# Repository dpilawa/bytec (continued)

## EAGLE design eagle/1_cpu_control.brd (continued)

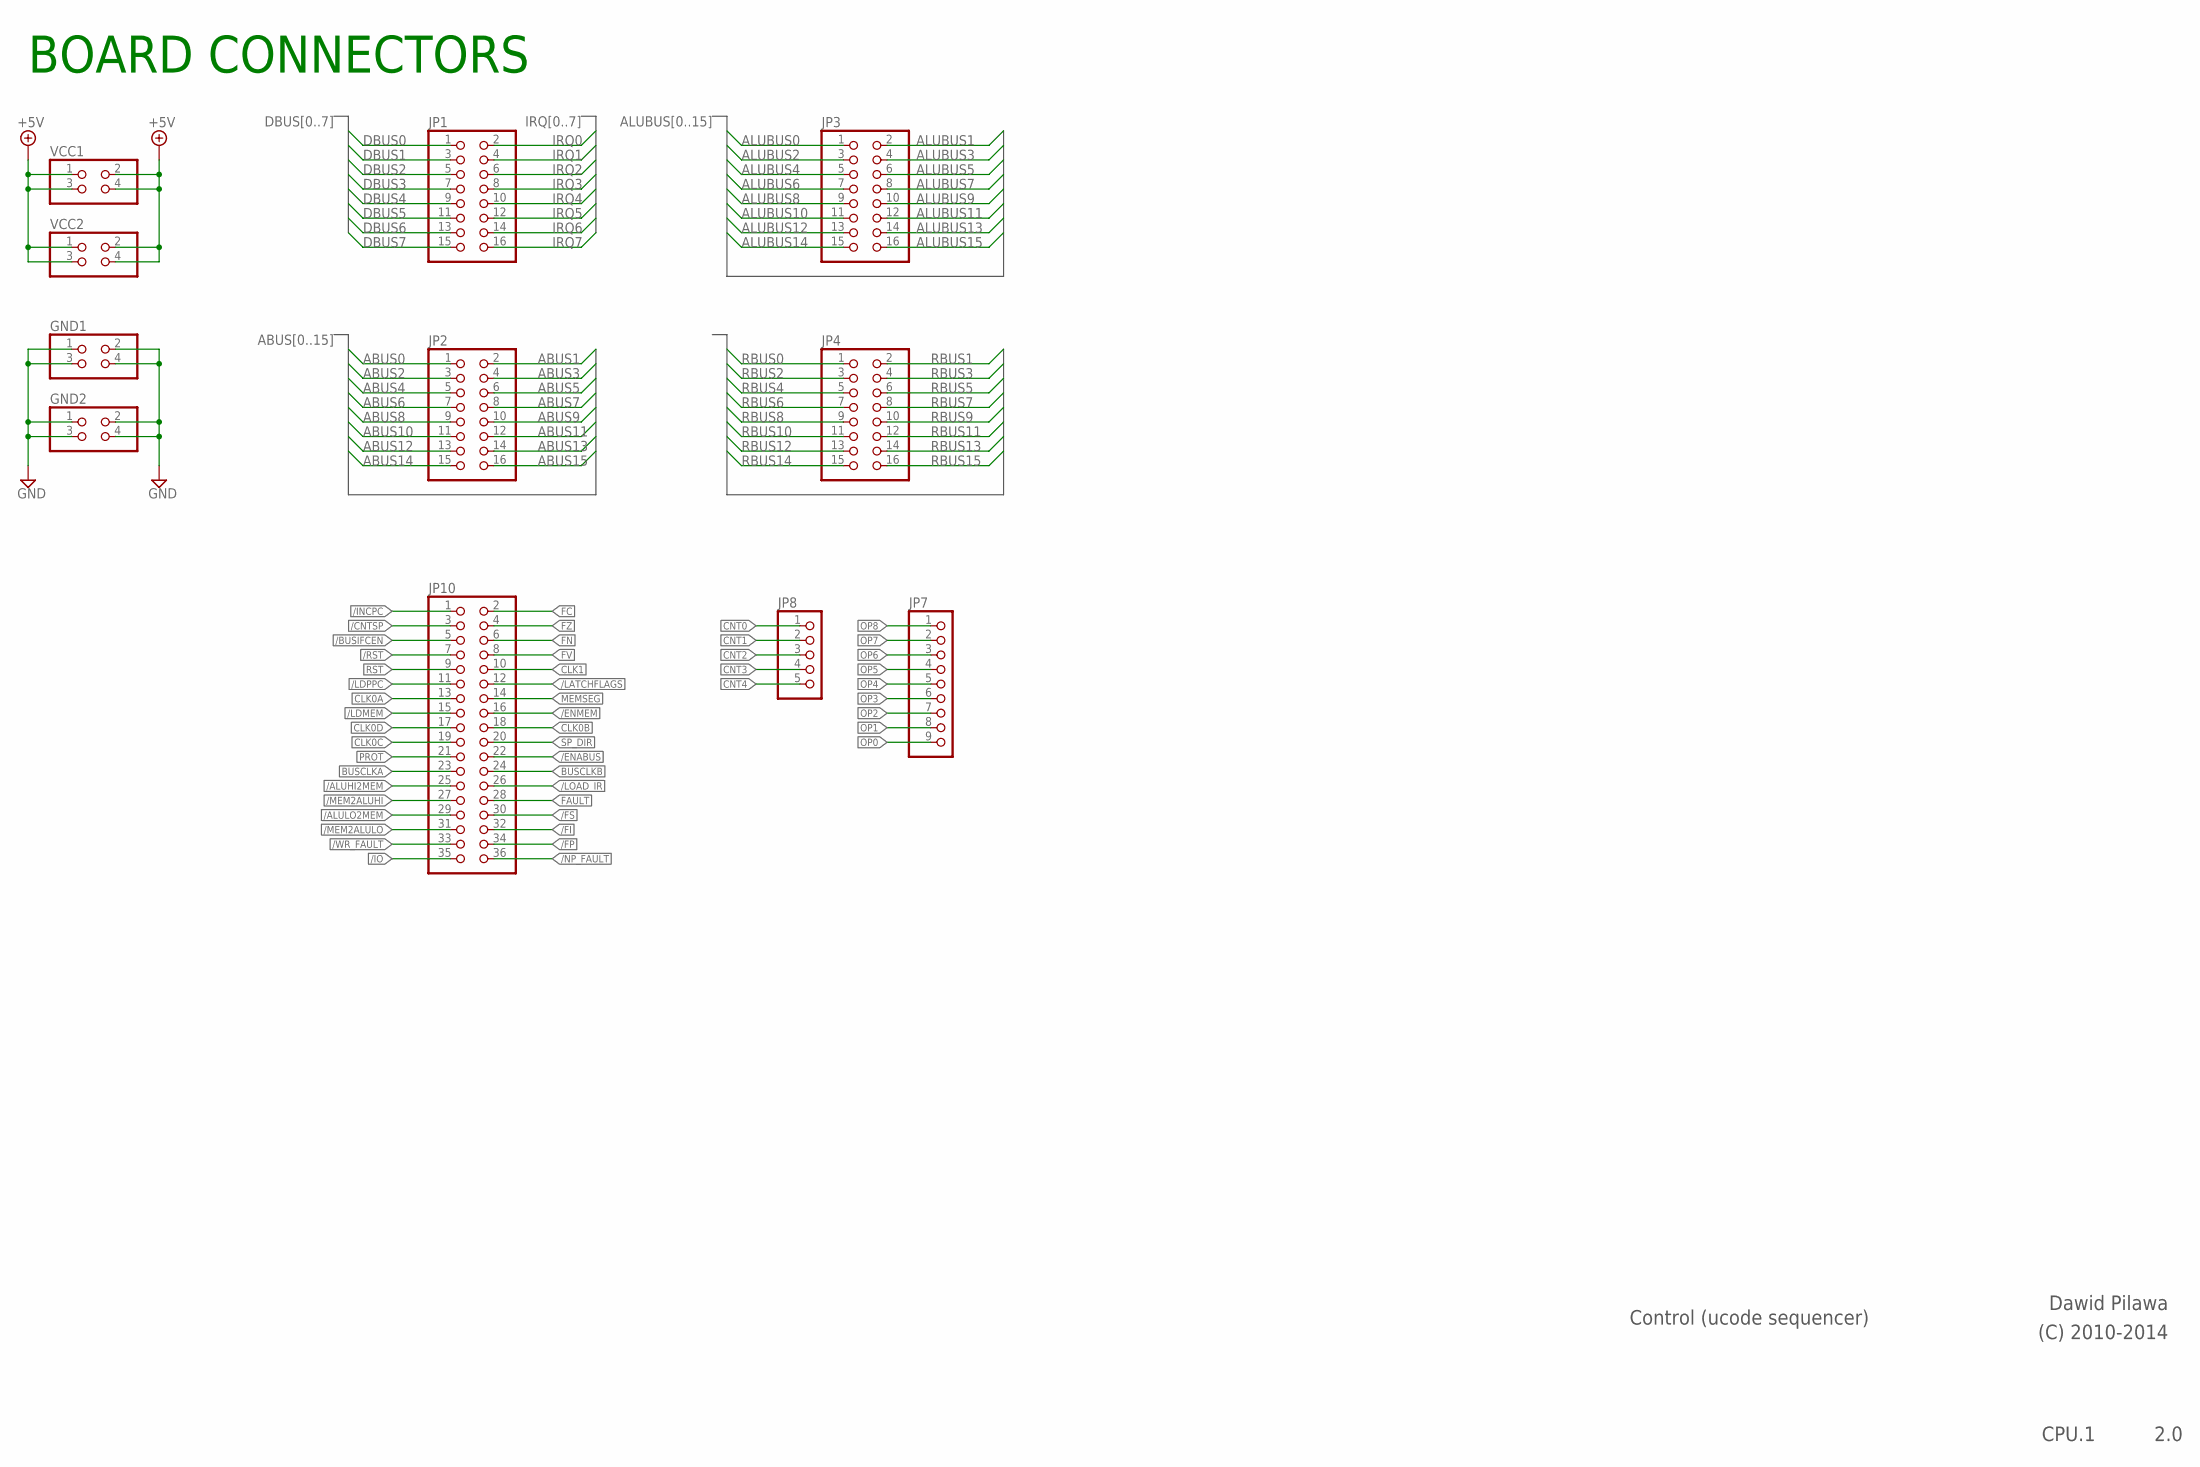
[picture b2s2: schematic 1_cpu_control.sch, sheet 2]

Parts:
GND1, GND2: PINHD-2X2; 2X02
JP1, JP2, JP3, JP4: PINHD-2X8; 2X08
JP7: PINHD-1X9; 1X09
JP8: PINHD-1X5; 1X05
JP10: PINHD-2X18; 2X18
VCC1, VCC2: PINHD-2X2; 2X02

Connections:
+5V: VCC1.1, VCC1.2, VCC1.3, VCC1.4, VCC2.1, VCC2.2, VCC2.3, VCC2.4; also elsewhere on the board
/ALUHI2MEM: JP10.25
/ALULO2MEM: JP10.29
/BUSIFCEN: JP10.5; also elsewhere on the board
/CNTSP: JP10.3
/ENABUS: JP10.22
/ENMEM: JP10.16
/FI: JP10.32; also elsewhere on the board
/FP: JP10.34
/FS: JP10.30; also elsewhere on the board
/INCPC: JP10.1
/IO: JP10.35
/LATCHFLAGS: JP10.12; also elsewhere on the board
/LDMEM: JP10.15
/LDPPC: JP10.11; also elsewhere on the board
/LOAD_IR: JP10.26; also elsewhere on the board
/MEM2ALUHI: JP10.27
/MEM2ALULO: JP10.31
/NP_FAULT: JP10.36; also elsewhere on the board
/RST: JP10.7; also elsewhere on the board
/WR_FAULT: JP10.33; also elsewhere on the board
ABUS0: JP2.1
ABUS1: JP2.2
ABUS2: JP2.3
ABUS3: JP2.4
ABUS4: JP2.5
ABUS5: JP2.6
ABUS6: JP2.7
ABUS7: JP2.8
ABUS8: JP2.9
ABUS9: JP2.10
ABUS10: JP2.11
ABUS11: JP2.12
ABUS12: JP2.13
ABUS13: JP2.14
ABUS14: JP2.15
ABUS15: JP2.16
ALUBUS0: JP3.1
ALUBUS1: JP3.2
ALUBUS2: JP3.3
ALUBUS3: JP3.4
ALUBUS4: JP3.5
ALUBUS5: JP3.6
ALUBUS6: JP3.7
ALUBUS7: JP3.8
ALUBUS8: JP3.9
ALUBUS9: JP3.10
ALUBUS10: JP3.11
ALUBUS11: JP3.12
ALUBUS12: JP3.13
ALUBUS13: JP3.14
ALUBUS14: JP3.15
ALUBUS15: JP3.16
BUSCLKA: JP10.23; also elsewhere on the board
BUSCLKB: JP10.24
CLK0A: JP10.13; also elsewhere on the board
CLK0B: JP10.18
CLK0C: JP10.19
CLK0D: JP10.17
CLK1: JP10.10
CNT0: JP8.1; also elsewhere on the board
CNT1: JP8.2; also elsewhere on the board
CNT2: JP8.3; also elsewhere on the board
CNT3: JP8.4; also elsewhere on the board
CNT4: JP8.5; also elsewhere on the board
DBUS0: JP1.1; also elsewhere on the board
DBUS1: JP1.3; also elsewhere on the board
DBUS2: JP1.5; also elsewhere on the board
DBUS3: JP1.7; also elsewhere on the board
DBUS4: JP1.9; also elsewhere on the board
DBUS5: JP1.11; also elsewhere on the board
DBUS6: JP1.13; also elsewhere on the board
DBUS7: JP1.15; also elsewhere on the board
FAULT: JP10.28; also elsewhere on the board
FC: JP10.2
FN: JP10.6
FV: JP10.8
FZ: JP10.4
GND: GND1.1, GND1.2, GND1.3, GND1.4, GND2.1, GND2.2, GND2.3, GND2.4; also elsewhere on the board
IRQ0: JP1.2; also elsewhere on the board
IRQ1: JP1.4; also elsewhere on the board
IRQ2: JP1.6; also elsewhere on the board
IRQ3: JP1.8; also elsewhere on the board
IRQ4: JP1.10; also elsewhere on the board
IRQ5: JP1.12; also elsewhere on the board
IRQ6: JP1.14; also elsewhere on the board
IRQ7: JP1.16; also elsewhere on the board
MEMSEG: JP10.14
OP0: JP7.9; also elsewhere on the board
OP1: JP7.8; also elsewhere on the board
OP2: JP7.7; also elsewhere on the board
OP3: JP7.6; also elsewhere on the board
OP4: JP7.5; also elsewhere on the board
OP5: JP7.4; also elsewhere on the board
OP6: JP7.3; also elsewhere on the board
OP7: JP7.2; also elsewhere on the board
OP8: JP7.1; also elsewhere on the board
PROT: JP10.21; also elsewhere on the board
RBUS0: JP4.1
RBUS1: JP4.2
RBUS2: JP4.3
RBUS3: JP4.4
RBUS4: JP4.5
RBUS5: JP4.6
RBUS6: JP4.7
RBUS7: JP4.8
RBUS8: JP4.9
RBUS9: JP4.10
RBUS10: JP4.11
RBUS11: JP4.12
RBUS12: JP4.13
RBUS13: JP4.14
RBUS14: JP4.15
RBUS15: JP4.16
RST: JP10.9; also elsewhere on the board
SP_DIR: JP10.20

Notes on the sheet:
Control (ucode sequencer)
2.0
Dawid Pilawa
(C) 2010-2014
CPU.1
BOARD CONNECTORS

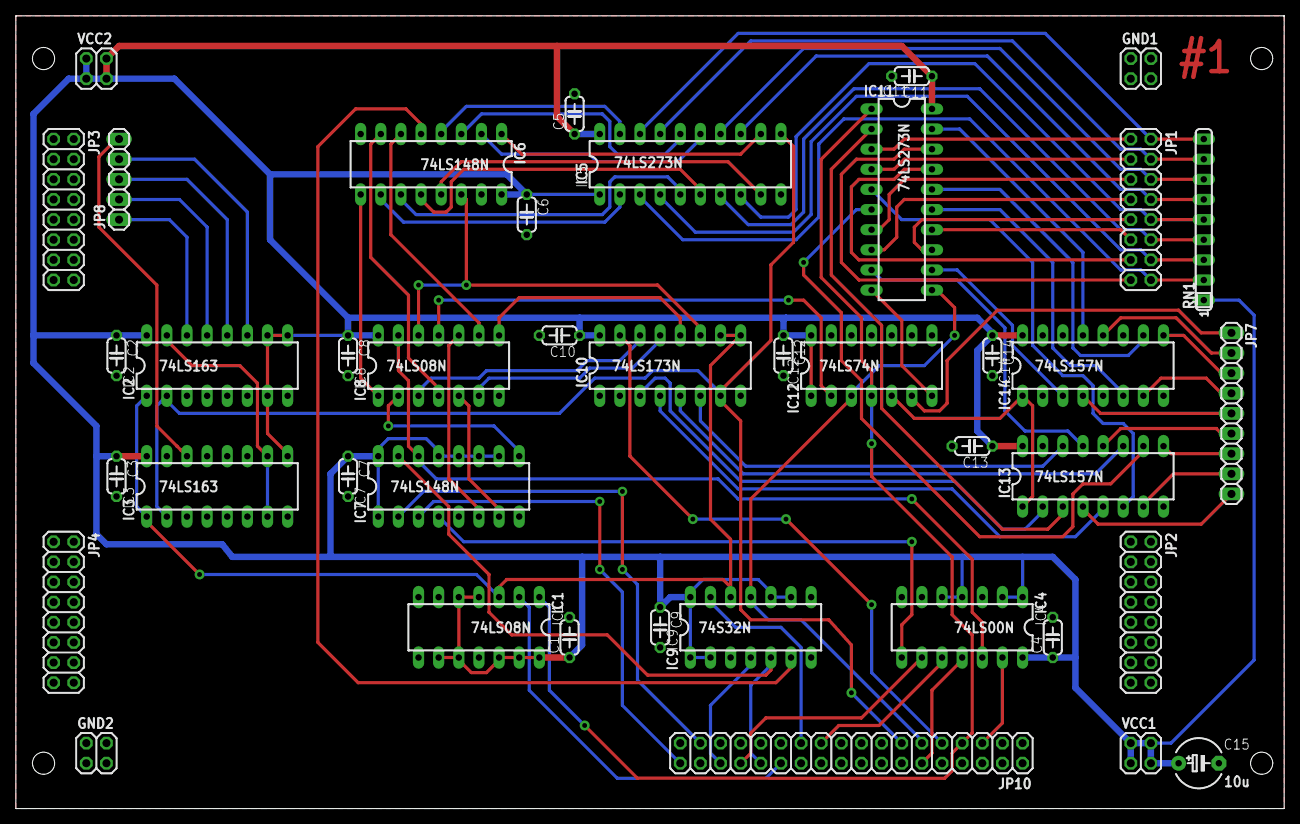
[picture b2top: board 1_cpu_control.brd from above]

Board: 2 copper layers, 160.0 x 100.0 mm, 41 parts (0 on the bottom side), 83 nets.

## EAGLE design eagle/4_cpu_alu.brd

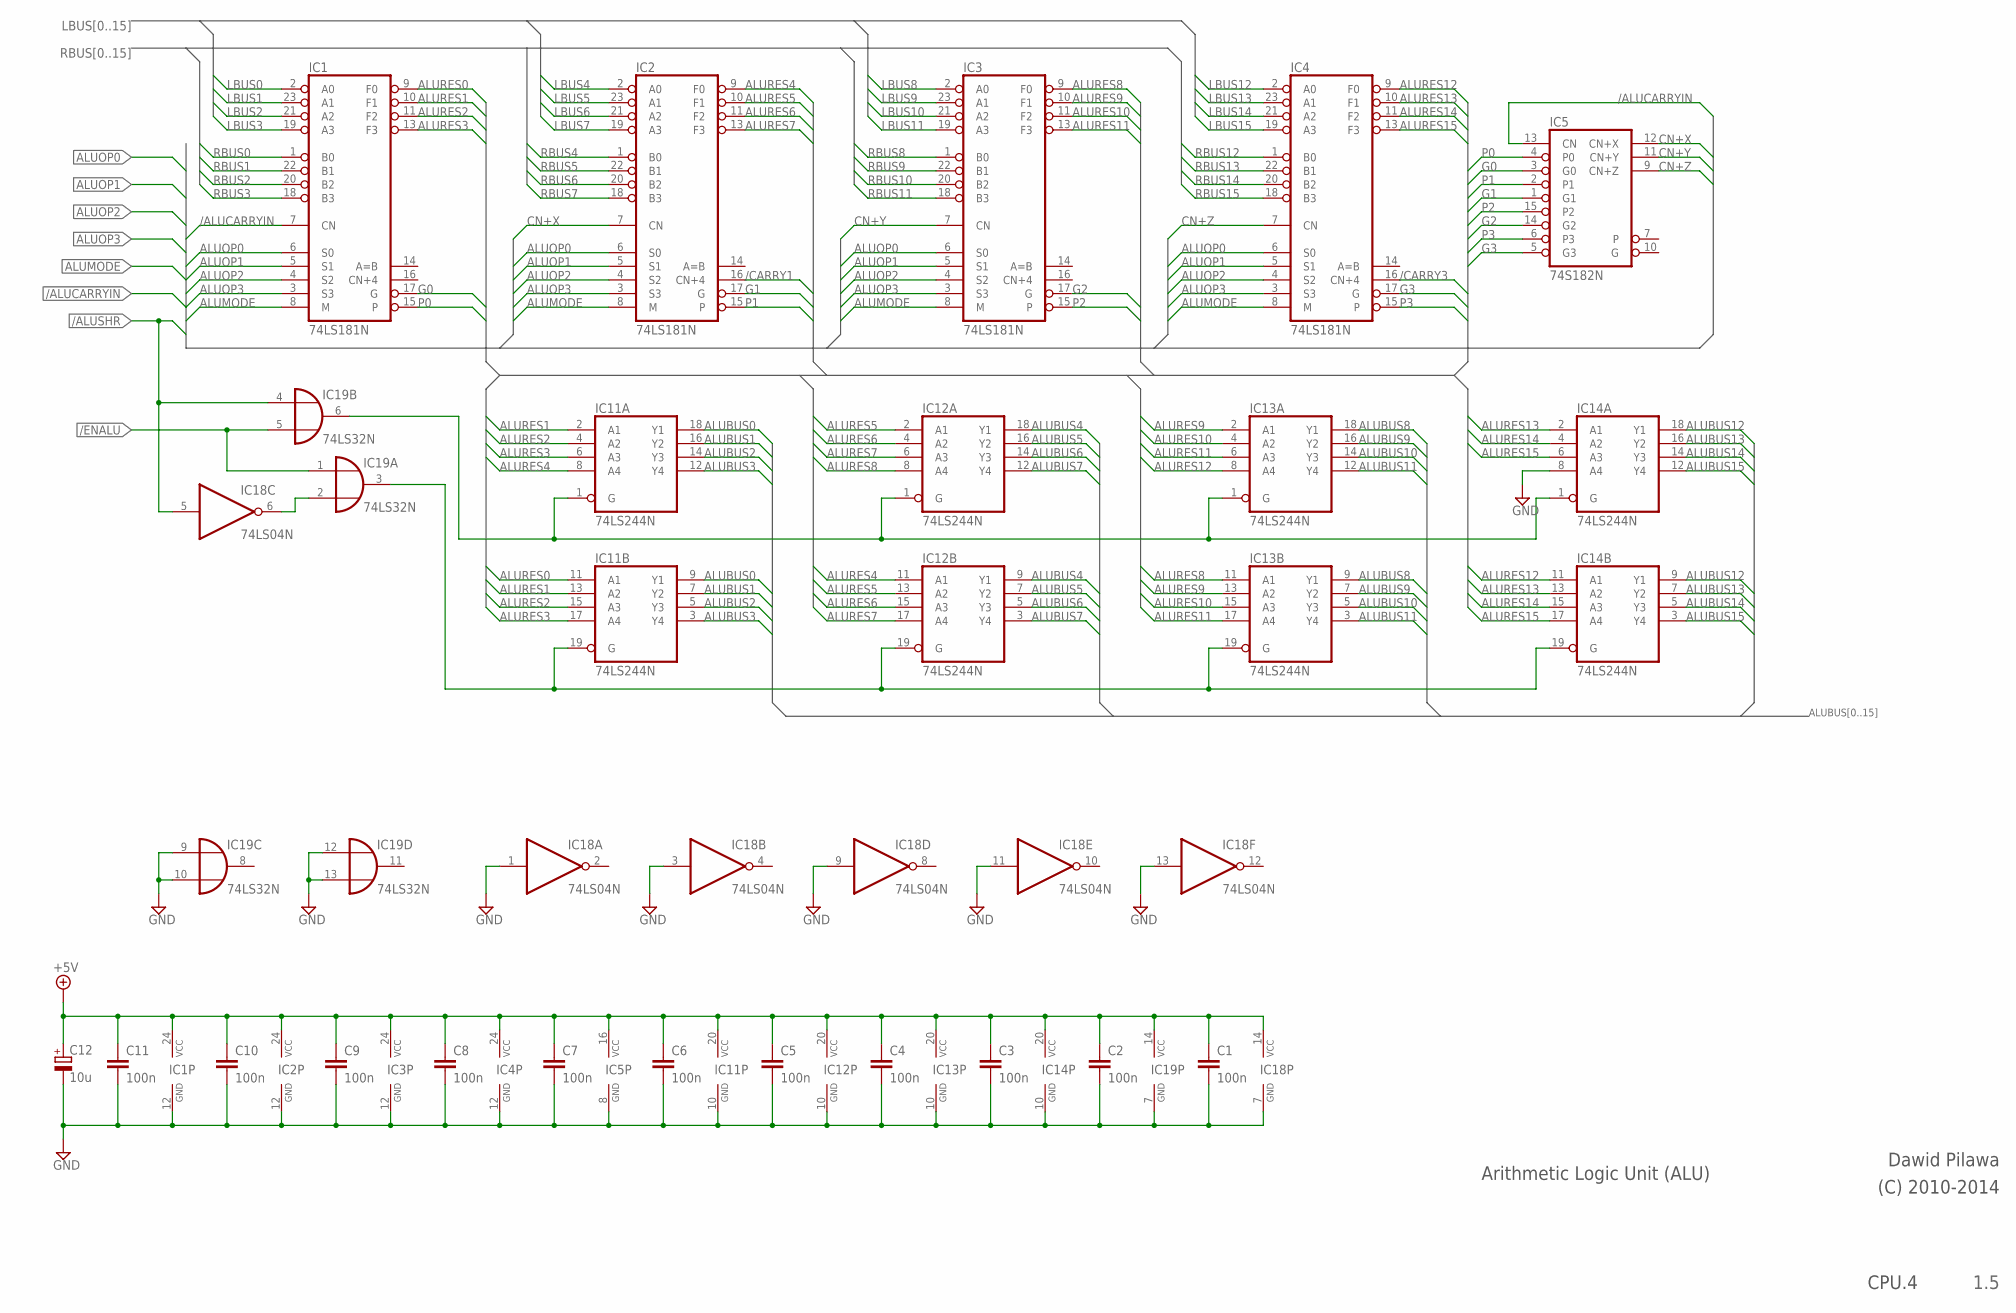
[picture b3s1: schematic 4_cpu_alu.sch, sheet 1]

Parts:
C1, C2, C3, C4, C5, C6, C7, C8, C9, C10, C11: 100n; C050-024X044
C12: 10u; E2,5-6
IC1, IC2, IC3, IC4: 74LS181N; DIL24-6
IC5: 74S182N; DIL16
IC11, IC12, IC13, IC14: 74LS244N; DIL20
IC18: 74LS04N; DIL14
IC19: 74LS32N; DIL14

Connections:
+5V: C1.1, C2.1, C3.1, C4.1, C5.1, C6.1, C7.1, C8.1, C9.1, C10.1, C11.1, C12.+, IC1.24 (VCC), IC2.24 (VCC), IC3.24 (VCC), IC4.24 (VCC), IC5.16 (VCC), IC11.20 (VCC), IC12.20 (VCC), IC13.20 (VCC), IC14.20 (VCC), IC18.14 (VCC), IC19.14 (VCC); also elsewhere on the board
/ALUCARRYIN: IC1.7 (CN), IC5.13 (CN); also elsewhere on the board
/ALUSHR: IC18.5 (I), IC19.4 (I0); also elsewhere on the board
/CARRY1: IC2.16 (CN+4); also elsewhere on the board
/CARRY3: IC4.16 (CN+4); also elsewhere on the board
/ENALU: IC19.1 (I0), IC19.5 (I1); also elsewhere on the board
ALUBUS0: IC11.9 (Y1), IC11.18 (Y1); also elsewhere on the board
ALUBUS1: IC11.7 (Y2), IC11.16 (Y2); also elsewhere on the board
ALUBUS2: IC11.5 (Y3), IC11.14 (Y3); also elsewhere on the board
ALUBUS3: IC11.3 (Y4), IC11.12 (Y4); also elsewhere on the board
ALUBUS4: IC12.9 (Y1), IC12.18 (Y1); also elsewhere on the board
ALUBUS5: IC12.7 (Y2), IC12.16 (Y2); also elsewhere on the board
ALUBUS6: IC12.5 (Y3), IC12.14 (Y3); also elsewhere on the board
ALUBUS7: IC12.3 (Y4), IC12.12 (Y4); also elsewhere on the board
ALUBUS8: IC13.9 (Y1), IC13.18 (Y1); also elsewhere on the board
ALUBUS9: IC13.7 (Y2), IC13.16 (Y2); also elsewhere on the board
ALUBUS10: IC13.5 (Y3), IC13.14 (Y3); also elsewhere on the board
ALUBUS11: IC13.3 (Y4), IC13.12 (Y4); also elsewhere on the board
ALUBUS12: IC14.9 (Y1), IC14.18 (Y1); also elsewhere on the board
ALUBUS13: IC14.7 (Y2), IC14.16 (Y2); also elsewhere on the board
ALUBUS14: IC14.5 (Y3), IC14.14 (Y3); also elsewhere on the board
ALUBUS15: IC14.3 (Y4), IC14.12 (Y4); also elsewhere on the board
ALUMODE: IC1.8 (M), IC2.8 (M), IC3.8 (M), IC4.8 (M); also elsewhere on the board
ALUOP0: IC1.6 (S0), IC2.6 (S0), IC3.6 (S0), IC4.6 (S0); also elsewhere on the board
ALUOP1: IC1.5 (S1), IC2.5 (S1), IC3.5 (S1), IC4.5 (S1); also elsewhere on the board
ALUOP2: IC1.4 (S2), IC2.4 (S2), IC3.4 (S2), IC4.4 (S2); also elsewhere on the board
ALUOP3: IC1.3 (S3), IC2.3 (S3), IC3.3 (S3), IC4.3 (S3); also elsewhere on the board
ALURES0: IC1.9 (F0), IC11.11 (A1); also elsewhere on the board
ALURES1: IC1.10 (F1), IC11.2 (A1), IC11.13 (A2)
ALURES2: IC1.11 (F2), IC11.4 (A2), IC11.15 (A3)
ALURES3: IC1.13 (F3), IC11.6 (A3), IC11.17 (A4)
ALURES4: IC2.9 (F0), IC11.8 (A4), IC12.11 (A1)
ALURES5: IC2.10 (F1), IC12.2 (A1), IC12.13 (A2)
ALURES6: IC2.11 (F2), IC12.4 (A2), IC12.15 (A3)
ALURES7: IC2.13 (F3), IC12.6 (A3), IC12.17 (A4)
ALURES8: IC3.9 (F0), IC12.8 (A4), IC13.11 (A1); also elsewhere on the board
ALURES9: IC3.10 (F1), IC13.2 (A1), IC13.13 (A2)
ALURES10: IC3.11 (F2), IC13.4 (A2), IC13.15 (A3)
ALURES11: IC3.13 (F3), IC13.6 (A3), IC13.17 (A4)
ALURES12: IC4.9 (F0), IC13.8 (A4), IC14.11 (A1)
ALURES13: IC4.10 (F1), IC14.2 (A1), IC14.13 (A2)
ALURES14: IC4.11 (F2), IC14.4 (A2), IC14.15 (A3)
ALURES15: IC4.13 (F3), IC14.6 (A3), IC14.17 (A4)
CN+X: IC2.7 (CN), IC5.12 (CN+X)
CN+Y: IC3.7 (CN), IC5.11 (CN+Y)
CN+Z: IC4.7 (CN), IC5.9 (CN+Z)
G0: IC1.17 (G), IC5.3 (G0)
G1: IC2.17 (G), IC5.1 (G1)
G2: IC3.17 (G), IC5.14 (G2)
G3: IC4.17 (G), IC5.5 (G3)
GND: C1.2, C2.2, C3.2, C4.2, C5.2, C6.2, C7.2, C8.2, C9.2, C10.2, C11.2, C12.-, IC1.12 (GND), IC2.12 (GND), IC3.12 (GND), IC4.12 (GND), IC5.8 (GND), IC11.10 (GND), IC12.10 (GND), IC13.10 (GND), IC14.8 (A4), IC14.10 (GND), IC18.1 (I), IC18.3 (I), IC18.7 (GND), IC18.9 (I), IC18.11 (I), IC18.13 (I), IC19.7 (GND), IC19.9 (I0), IC19.10 (I1), IC19.12 (I0), IC19.13 (I1); also elsewhere on the board
LBUS0: IC1.2 (A0); also elsewhere on the board
LBUS1: IC1.23 (A1); also elsewhere on the board
LBUS2: IC1.21 (A2); also elsewhere on the board
LBUS3: IC1.19 (A3); also elsewhere on the board
LBUS4: IC2.2 (A0); also elsewhere on the board
LBUS5: IC2.23 (A1); also elsewhere on the board
LBUS6: IC2.21 (A2); also elsewhere on the board
LBUS7: IC2.19 (A3); also elsewhere on the board
LBUS8: IC3.2 (A0); also elsewhere on the board
LBUS9: IC3.23 (A1); also elsewhere on the board
LBUS10: IC3.21 (A2); also elsewhere on the board
LBUS11: IC3.19 (A3); also elsewhere on the board
LBUS12: IC4.2 (A0); also elsewhere on the board
LBUS13: IC4.23 (A1); also elsewhere on the board
LBUS14: IC4.21 (A2); also elsewhere on the board
LBUS15: IC4.19 (A3); also elsewhere on the board
unnamed: IC11.1 (G), IC12.1 (G), IC13.1 (G), IC14.1 (G), IC19.6 (O)
unnamed: IC18.6 (O), IC19.2 (I1)
unnamed: IC11.19 (G), IC12.19 (G), IC13.19 (G), IC14.19 (G), IC19.3 (O)
P0: IC1.15, IC5.4 (P0)
P1: IC2.15, IC5.2 (P1)
P2: IC3.15, IC5.15 (P2)
P3: IC4.15, IC5.6 (P3)
RBUS0: IC1.1 (B0); also elsewhere on the board
RBUS1: IC1.22 (B1); also elsewhere on the board
RBUS2: IC1.20 (B2); also elsewhere on the board
RBUS3: IC1.18 (B3); also elsewhere on the board
RBUS4: IC2.1 (B0); also elsewhere on the board
RBUS5: IC2.22 (B1); also elsewhere on the board
RBUS6: IC2.20 (B2); also elsewhere on the board
RBUS7: IC2.18 (B3); also elsewhere on the board
RBUS8: IC3.1 (B0); also elsewhere on the board
RBUS9: IC3.22 (B1); also elsewhere on the board
RBUS10: IC3.20 (B2); also elsewhere on the board
RBUS11: IC3.18 (B3); also elsewhere on the board
RBUS12: IC4.1 (B0); also elsewhere on the board
RBUS13: IC4.22 (B1); also elsewhere on the board
RBUS14: IC4.20 (B2); also elsewhere on the board
RBUS15: IC4.18 (B3); also elsewhere on the board

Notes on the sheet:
Arithmetic Logic Unit (ALU)
Dawid Pilawa
(C) 2010-2014
1.5
CPU.4

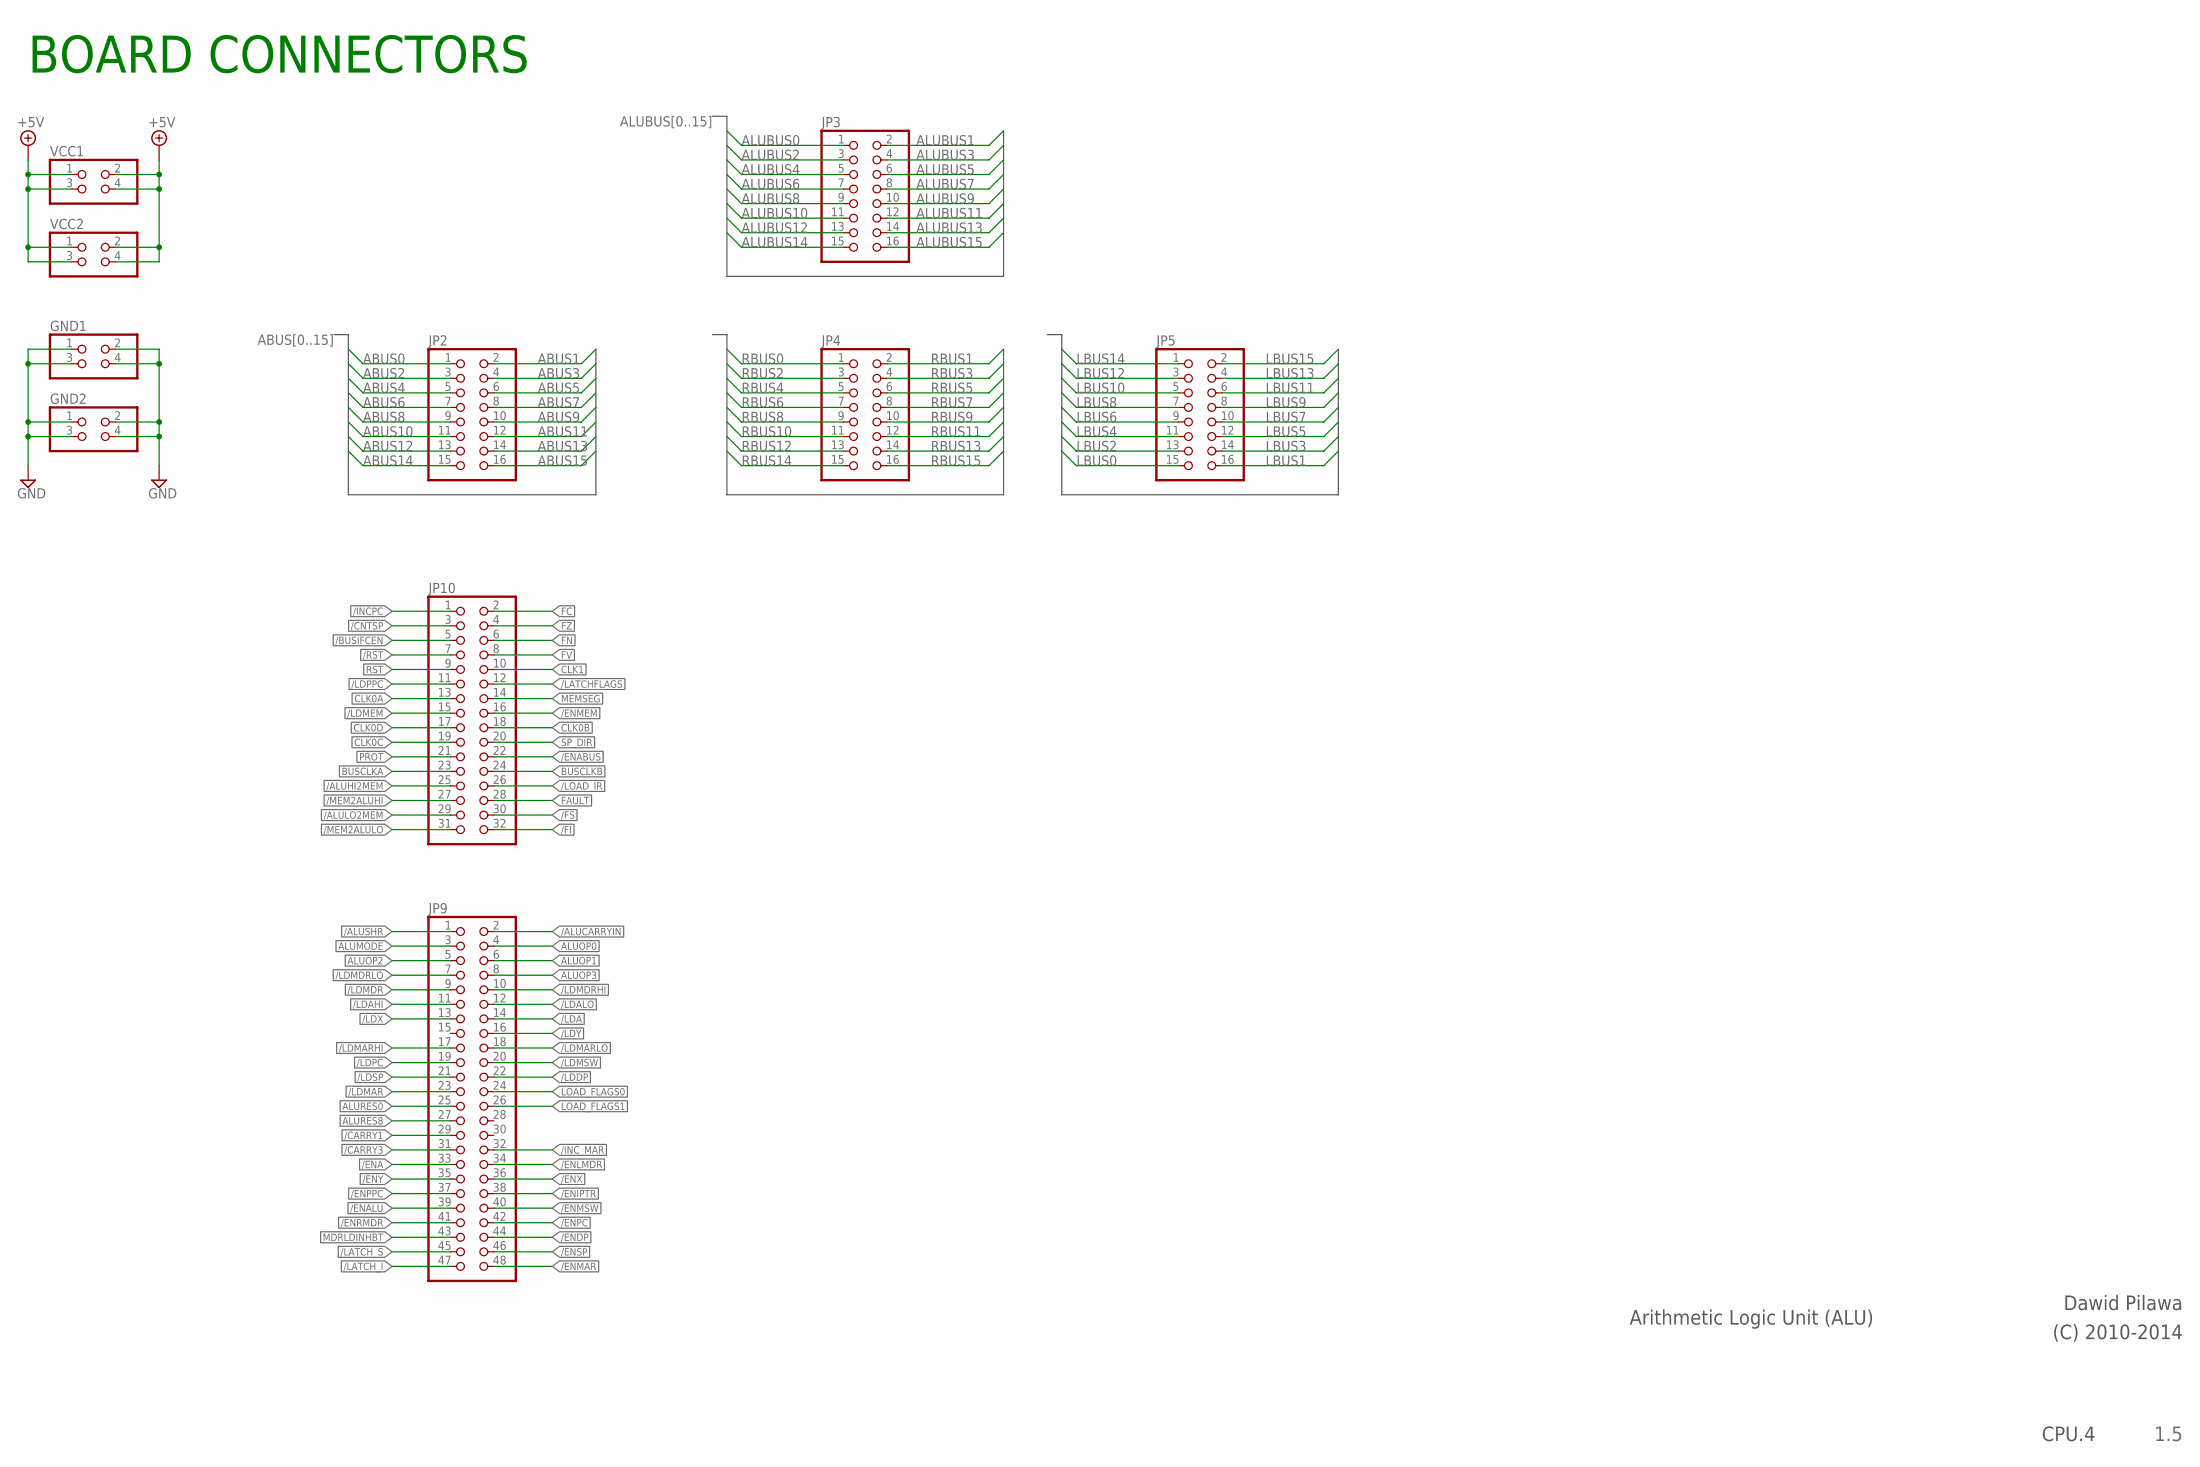
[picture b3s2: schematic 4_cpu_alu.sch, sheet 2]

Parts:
GND1, GND2: PINHD-2X2; 2X02
JP2, JP3, JP4, JP5: PINHD-2X8; 2X08
JP9: PINHD-2X24; 2X24
JP10: PINHD-2X16; 2X16
VCC1, VCC2: PINHD-2X2; 2X02

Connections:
+5V: VCC1.1, VCC1.2, VCC1.3, VCC1.4, VCC2.1, VCC2.2, VCC2.3, VCC2.4; also elsewhere on the board
/ALUCARRYIN: JP9.2; also elsewhere on the board
/ALUHI2MEM: JP10.25
/ALULO2MEM: JP10.29
/ALUSHR: JP9.1; also elsewhere on the board
/BUSIFCEN: JP10.5
/CARRY1: JP9.29; also elsewhere on the board
/CARRY3: JP9.31; also elsewhere on the board
/CNTSP: JP10.3
/ENA: JP9.33
/ENABUS: JP10.22
/ENALU: JP9.39; also elsewhere on the board
/ENDP: JP9.44
/ENIPTR: JP9.38
/ENLMDR: JP9.34
/ENMAR: JP9.48
/ENMEM: JP10.16
/ENMSW: JP9.40
/ENPC: JP9.42
/ENPPC: JP9.37
/ENRMDR: JP9.41
/ENSP: JP9.46
/ENX: JP9.36
/ENY: JP9.35
/FI: JP10.32
/FS: JP10.30
/INCPC: JP10.1
/INC_MAR: JP9.32
/LATCHFLAGS: JP10.12
/LATCH_I: JP9.47
/LATCH_S: JP9.45
/LDA: JP9.14
/LDAHI: JP9.11
/LDALO: JP9.12
/LDDP: JP9.22
/LDMAR: JP9.23
/LDMARHI: JP9.17
/LDMARLO: JP9.18
/LDMDR: JP9.9
/LDMDRHI: JP9.10
/LDMDRLO: JP9.7
/LDMEM: JP10.15
/LDMSW: JP9.20
/LDPC: JP9.19
/LDSP: JP9.21
/LDX: JP9.13
/LDY: JP9.16
/LOAD_IR: JP10.26
/MEM2ALUHI: JP10.27
/MEM2ALULO: JP10.31
/RST: JP10.7
ABUS0: JP2.1
ABUS1: JP2.2
ABUS2: JP2.3
ABUS3: JP2.4
ABUS4: JP2.5
ABUS5: JP2.6
ABUS6: JP2.7
ABUS7: JP2.8
ABUS8: JP2.9
ABUS9: JP2.10
ABUS10: JP2.11
ABUS11: JP2.12
ABUS12: JP2.13
ABUS13: JP2.14
ABUS14: JP2.15
ABUS15: JP2.16
ALUBUS0: JP3.1; also elsewhere on the board
ALUBUS1: JP3.2; also elsewhere on the board
ALUBUS2: JP3.3; also elsewhere on the board
ALUBUS3: JP3.4; also elsewhere on the board
ALUBUS4: JP3.5; also elsewhere on the board
ALUBUS5: JP3.6; also elsewhere on the board
ALUBUS6: JP3.7; also elsewhere on the board
ALUBUS7: JP3.8; also elsewhere on the board
ALUBUS8: JP3.9; also elsewhere on the board
ALUBUS9: JP3.10; also elsewhere on the board
ALUBUS10: JP3.11; also elsewhere on the board
ALUBUS11: JP3.12; also elsewhere on the board
ALUBUS12: JP3.13; also elsewhere on the board
ALUBUS13: JP3.14; also elsewhere on the board
ALUBUS14: JP3.15; also elsewhere on the board
ALUBUS15: JP3.16; also elsewhere on the board
ALUMODE: JP9.3; also elsewhere on the board
ALUOP0: JP9.4; also elsewhere on the board
ALUOP1: JP9.6; also elsewhere on the board
ALUOP2: JP9.5; also elsewhere on the board
ALUOP3: JP9.8; also elsewhere on the board
ALURES0: JP9.25; also elsewhere on the board
ALURES8: JP9.27; also elsewhere on the board
BUSCLKA: JP10.23
BUSCLKB: JP10.24
CLK0A: JP10.13
CLK0B: JP10.18
CLK0C: JP10.19
CLK0D: JP10.17
CLK1: JP10.10
FAULT: JP10.28
FC: JP10.2
FN: JP10.6
FV: JP10.8
FZ: JP10.4
GND: GND1.1, GND1.2, GND1.3, GND1.4, GND2.1, GND2.2, GND2.3, GND2.4; also elsewhere on the board
LBUS0: JP5.15; also elsewhere on the board
LBUS1: JP5.16; also elsewhere on the board
LBUS2: JP5.13; also elsewhere on the board
LBUS3: JP5.14; also elsewhere on the board
LBUS4: JP5.11; also elsewhere on the board
LBUS5: JP5.12; also elsewhere on the board
LBUS6: JP5.9; also elsewhere on the board
LBUS7: JP5.10; also elsewhere on the board
LBUS8: JP5.7; also elsewhere on the board
LBUS9: JP5.8; also elsewhere on the board
LBUS10: JP5.5; also elsewhere on the board
LBUS11: JP5.6; also elsewhere on the board
LBUS12: JP5.3; also elsewhere on the board
LBUS13: JP5.4; also elsewhere on the board
LBUS14: JP5.1; also elsewhere on the board
LBUS15: JP5.2; also elsewhere on the board
LOAD_FLAGS0: JP9.24
LOAD_FLAGS1: JP9.26
MDRLDINHBT: JP9.43
MEMSEG: JP10.14
PROT: JP10.21
RBUS0: JP4.1; also elsewhere on the board
RBUS1: JP4.2; also elsewhere on the board
RBUS2: JP4.3; also elsewhere on the board
RBUS3: JP4.4; also elsewhere on the board
RBUS4: JP4.5; also elsewhere on the board
RBUS5: JP4.6; also elsewhere on the board
RBUS6: JP4.7; also elsewhere on the board
RBUS7: JP4.8; also elsewhere on the board
RBUS8: JP4.9; also elsewhere on the board
RBUS9: JP4.10; also elsewhere on the board
RBUS10: JP4.11; also elsewhere on the board
RBUS11: JP4.12; also elsewhere on the board
RBUS12: JP4.13; also elsewhere on the board
RBUS13: JP4.14; also elsewhere on the board
RBUS14: JP4.15; also elsewhere on the board
RBUS15: JP4.16; also elsewhere on the board
RST: JP10.9
SP_DIR: JP10.20

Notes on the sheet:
Arithmetic Logic Unit (ALU)
Dawid Pilawa
(C) 2010-2014
1.5
CPU.4
BOARD CONNECTORS

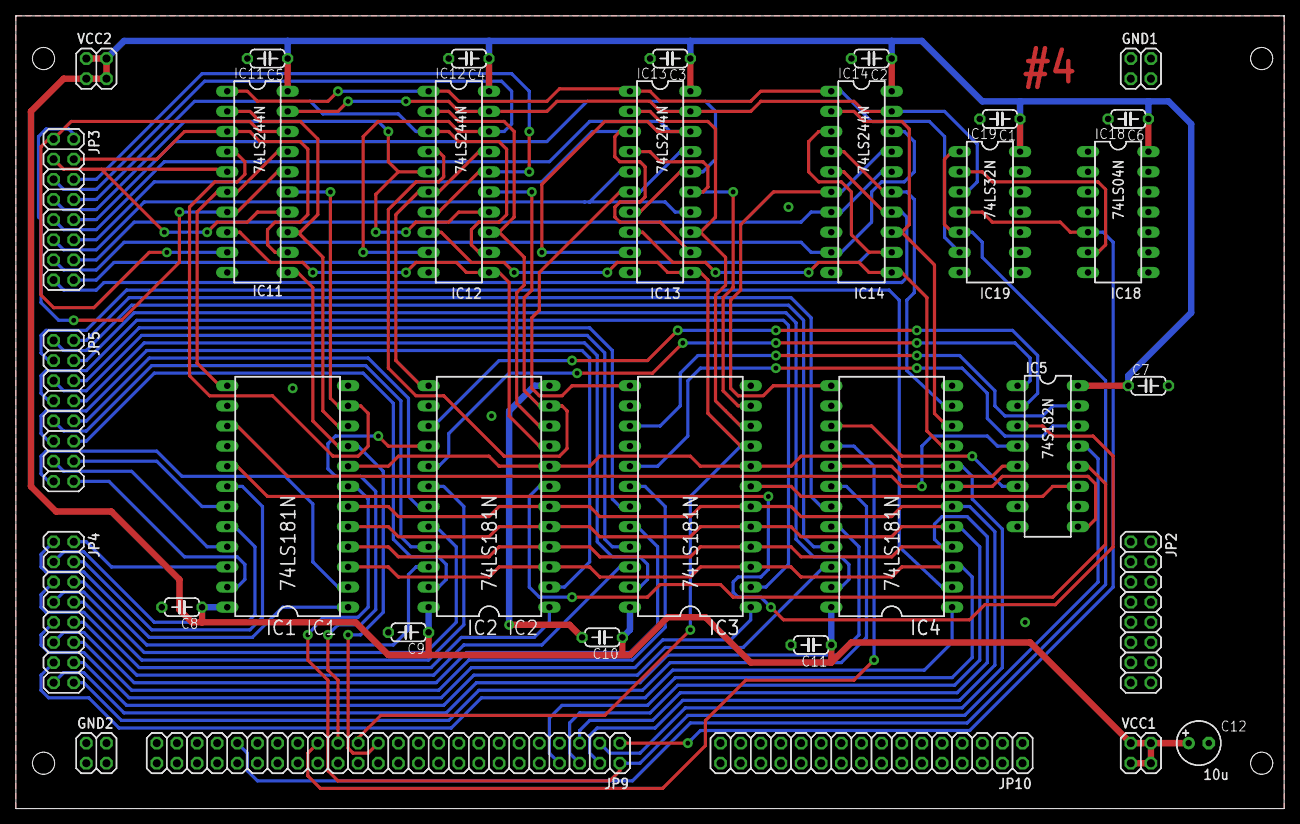
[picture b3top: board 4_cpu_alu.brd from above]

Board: 2 copper layers, 160.0 x 100.0 mm, 33 parts (0 on the bottom side), 90 nets.
